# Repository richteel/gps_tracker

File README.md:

# gps_tracker
GPS Tracker and data logger

The files here include hardware, case, PCB, Python and C++ code, documentation, and reference files.

## Bill of Materials (BOM) ##
- Adafruit Feather RP2040
	- Qty: 1
	- Source: Adafruit [https://www.adafruit.com/product/4884](https://www.adafruit.com/product/4884 "Adafruit Feather RP2040")
- Adafruit Micro SD Breakout
	- Qty: 1
	- Source: Adafruit [https://www.adafruit.com/product/4682](https://www.adafruit.com/product/4682 "Adafruit Micro SD SPI or SDIO Card Breakout Board - 3V ONLY!")
- SPDT Slide Switch
	- Qty: 2
	- Source: Adafruit [https://www.adafruit.com/product/805](https://www.adafruit.com/product/805 "SPDT Slide Switch")
- Tactile Switch Push Button (6mm slim)
	- Qty: 4
	- Source: Adafruit [https://www.adafruit.com/product/1489](https://www.adafruit.com/product/1489 "Tactile Switch Push Button (6mm slim)")
- ST-PH 2-Pin SMT Right Angle Connector
	- Qty: 1
	- Source: Adafruit [https://www.adafruit.com/product/1769](https://www.adafruit.com/product/1769 "ST-PH 2-Pin SMT Right Angle Connector")
- GPS Receiver - GP-635T (50 Channel)
	- Qty: 1
	- Source: Sparkfun [https://www.sparkfun.com/products/retired/11571](https://www.sparkfun.com/products/retired/11571 "GPS Receiver - GP-635T (50 Channel)")
- JST SH Jumper 6 Wire Assembly - 8"
	- Qty: 1
	- Source: Sparkfun [https://www.sparkfun.com/products/10361](https://www.sparkfun.com/products/10361 "JST SH Jumper 6 Wire Assembly - 8 inch")
- I2C 128x64 OLED Display
	- Qty: 1
	- Source: Amazon [https://www.amazon.com/gp/product/B08VNRH5HR/ref=ppx_yo_dt_b_search_asin_title?ie=UTF8&th=1](https://www.amazon.com/gp/product/B08VNRH5HR/ref=ppx_yo_dt_b_search_asin_title?ie=UTF8&th=1 "I2C 128x64 OLED Display")
- 3.7V 680mAh 102530 Lipo Battery Rechargeable Lithium Polymer ion Battery Pack with JST Connector
	- Qty: 1
	- Source: Amazon [https://www.amazon.com/gp/product/B07BTPNS2B/ref=ppx_yo_dt_b_search_asin_title?ie=UTF8&psc=1](https://www.amazon.com/gp/product/B07BTPNS2B/ref=ppx_yo_dt_b_search_asin_title?ie=UTF8&psc=1 "3.7V 680mAh 102530 Lipo Battery Rechargeable Lithium Polymer ion Battery Pack with JST Connector")
	- **WARNING:** The battery from this source has reversed polarity. Change the pins to match correct orientation!
- CR2032 Coin Button Cell Battery Holder Case
	- Qty: 1
	- Source: Amazon [https://www.amazon.com/gp/product/B06XF3K4NP/ref=ppx_yo_dt_b_search_asin_image?ie=UTF8&psc=1](https://www.amazon.com/gp/product/B06XF3K4NP/ref=ppx_yo_dt_b_search_asin_image?ie=UTF8&psc=1 "CR2032 Coin Button Cell Battery Holder Case")
- CR2032 Battery
	- Qty: 1
	- Source: Battery Junction [https://www.batteryjunction.com/sony-cr2032-5pack](https://www.batteryjunction.com/sony-cr2032-5pack "CR2032 Battery")
- Resistor 4.7K Ω (0805 package)
	- Qty: 4
	- Source: DigiKey [https://www.digikey.com/en/products/filter/chip-resistor-surface-mount/52...](https://www.digikey.com/en/products/filter/chip-resistor-surface-mount/52?s=N4IgjCBcoEwAwA4CsVQGMoDMCGAbAzgKYA0IA9lANogAsAdAOwAEA1gPIAWAtviALqkADgBcoIAKoA7AJbC2mALKFs%2BAK4AnQiAC%2BpALQxUIDJGHrVJclRAo%2BukHoCcRk2YukKkahDv3DXkEQ4JCZNfGl8YTJ1flIUaBBBKDAhJMgYJHsANiNpABMxPTA4CCFRSBAQUmEAT0EtCpUMbW0gA ""Filter for Resistor 4.7K Ω (0805 package)")
- Resistor 2M Ω (0805 package)
	- Qty: 4
	- Source: DigiKey [https://www.digikey.com/en/products/filter/chip-resistor-surface-mount/52...](https://www.digikey.com/en/products/filter/chip-resistor-surface-mount/52?s=N4IgjCBcoEwAwA4CsVQGMoDMCGAbAzgKYA0IA9lANogwAEAsgPIAWAtviALqkAOALlBABVAHYBLPo0z1C2fAFcAToRABfUgFoYqEBkh9F8kuSogUndSA0BOHXoNHSFSNQgXL2lyERwktZfhi%2BHxkilykKNAgPFBgvDGQMEiWAGw6YgAmghpgcBC8ApAgIKR8AJ48KkVyGKqqQA ""Filter for Resistor 2M Ω (0805 package)") 
- Capacitor 0.1μF (0805 package)
	- Qty: 2
	- Source: DigiKey [https://www.digikey.com/en/products/filter/ceramic-capacitors/60...](https://www.digikey.com/en/products/filter/ceramic-capacitors/60?s=N4IgjCBcoEwAwBYCcVQGMoDMCGAbAzgKYA0IA9lANohwB0YABAK0BiIAuqQA4AuUIAVQB2ASx4B5TAFlC2fAFcAToRABfUgFoYqEBkg9F8kuSogArB3UgNKaLqgGjpCpGoR2qq9tc0AHHDMGAGFsLmw0MTJFDlIANh0RABN%2BDTA4CG4%2BSBAQUh4ATy4VbLkMTyA "Filter for Capacitor 0.1μF (0805 package)")
- PCB
	- Qty: 1
	- Source: Shared on OSH Park [https://oshpark.com/shared_projects/GzuBZVdm](https://oshpark.com/shared_projects/GzuBZVdm "PCB")

# Log File #

The GPS Log Files are named with the format of YYYYMMDD.txt, where the letters are the following:

- YYYY: 4-digit Year
- MM: 2-digit Month
- DD: 2-digit Day

The data is comma separated, with the following columns.

- ISO 8601 formatted time-stamp (UTC) e.g. 2009-10-17T18:37:26Z
- Latitude in Degrees
- Longitude in Degrees
- Elevation in Meters
- Heading in Degrees
- Speed in Kpm

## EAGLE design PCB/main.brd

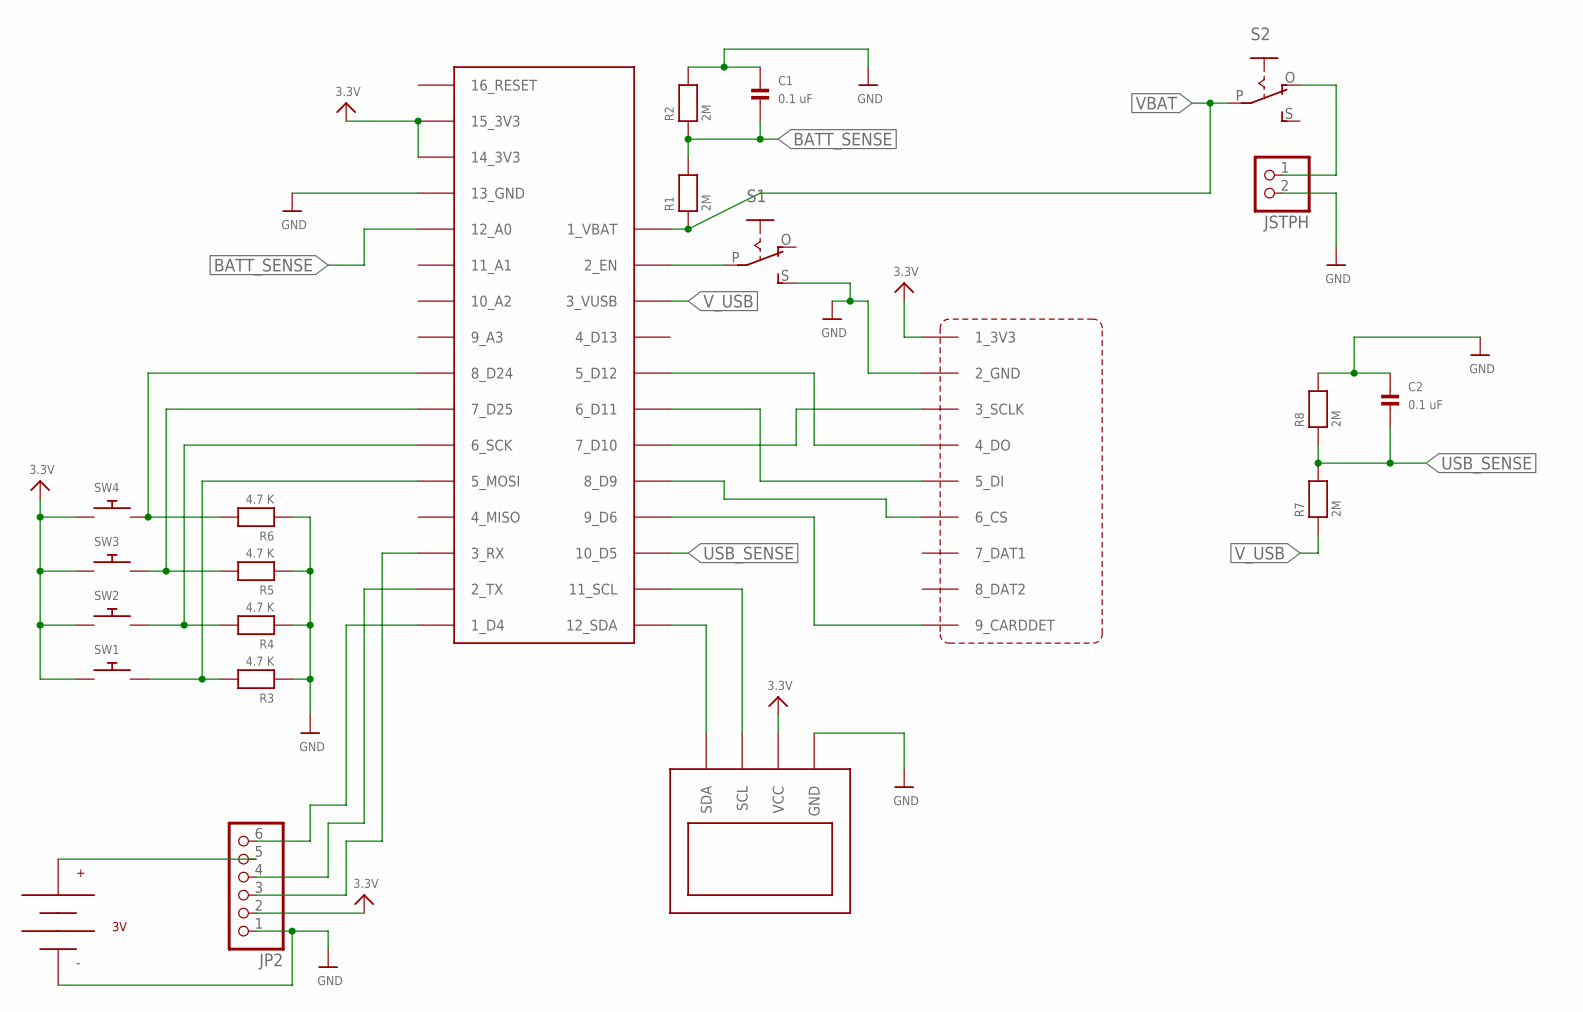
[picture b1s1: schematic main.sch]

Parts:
BAT_1: CR2032_HOLDER_WMYCONGCONG
C1, C2: 0.1 uF; _0805
FEATHER_RP2040: ADAFRUIT_FEATHER_RP2040; ADAFRUIT_FEATHER
JP2: HEADER-1X6ROUND; 1X06_ROUND
JSTPH: JST_2PIN-SMT-RA; JST-PH-2-SMT-RA
R1, R2, R7, R8: 2M; 0805
R3, R4, R5, R6: 4.7 K; 0805
S1, S2: EG1218S; EG1218
SDCARD2: ADAFRUIT_SDCARD3V3BOTTOM_MNT; ADAFRUIT_SDCARD3V3_B
SW1, SW2, SW3, SW4: SWITCH_PUSHBUTTONEVQ-PE; TACT_PANA-EVQ
U$10: OLED_SDD1306_128X64FRIENDA; OLED_SDD1306_128X64

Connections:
3.3V: FEATHER_RP2040.14_3V3, FEATHER_RP2040.15_3V3, JP2.2, SDCARD2.1_3V3, SW1.P$1, SW2.P$1, SW3.P$1, SW4.P$1, U$10.2_VCC (VCC)
BATT_SENSE: C1.2, FEATHER_RP2040.12_A0, R1.2, R2.1
GND: BAT_1.V- (-), C1.1, C2.1, FEATHER_RP2040.13_GND, JP2.1, JSTPH.2 (1), R2.2, R3.1, R4.1, R5.1, R6.1, R8.2, S1.S, SDCARD2.2_GND, U$10.1_GND (GND)
unnamed: FEATHER_RP2040.9_D6, SDCARD2.9_CARDDET
unnamed: FEATHER_RP2040.5_D12, SDCARD2.4_DO
unnamed: FEATHER_RP2040.7_D10, SDCARD2.3_SCLK
unnamed: FEATHER_RP2040.6_D11, SDCARD2.5_DI
unnamed: FEATHER_RP2040.8_D9, SDCARD2.6_CS
unnamed: FEATHER_RP2040.2_EN, S1.P
unnamed: FEATHER_RP2040.8_D24, R6.2, SW4.P$2
unnamed: FEATHER_RP2040.7_D25, R5.2, SW3.P$2
unnamed: FEATHER_RP2040.6_SCK, R4.2, SW2.P$2
unnamed: FEATHER_RP2040.5_MOSI, R3.2, SW1.P$2
unnamed: BAT_1.V+ (+), JP2.5
unnamed: FEATHER_RP2040.12_SDA, U$10.4_SDA (SDA)
unnamed: FEATHER_RP2040.11_SCL, U$10.3_SCL (SCL)
unnamed: JSTPH.1 (2), S2.O
unnamed: FEATHER_RP2040.3_RX, JP2.3
unnamed: FEATHER_RP2040.2_TX, JP2.4
unnamed: FEATHER_RP2040.1_D4, JP2.6
USB_SENSE: C2.2, FEATHER_RP2040.10_D5, R7.2, R8.1
VBAT: FEATHER_RP2040.1_VBAT, R1.1, S2.P
V_USB: FEATHER_RP2040.3_VBUS (3_VUSB), R7.1

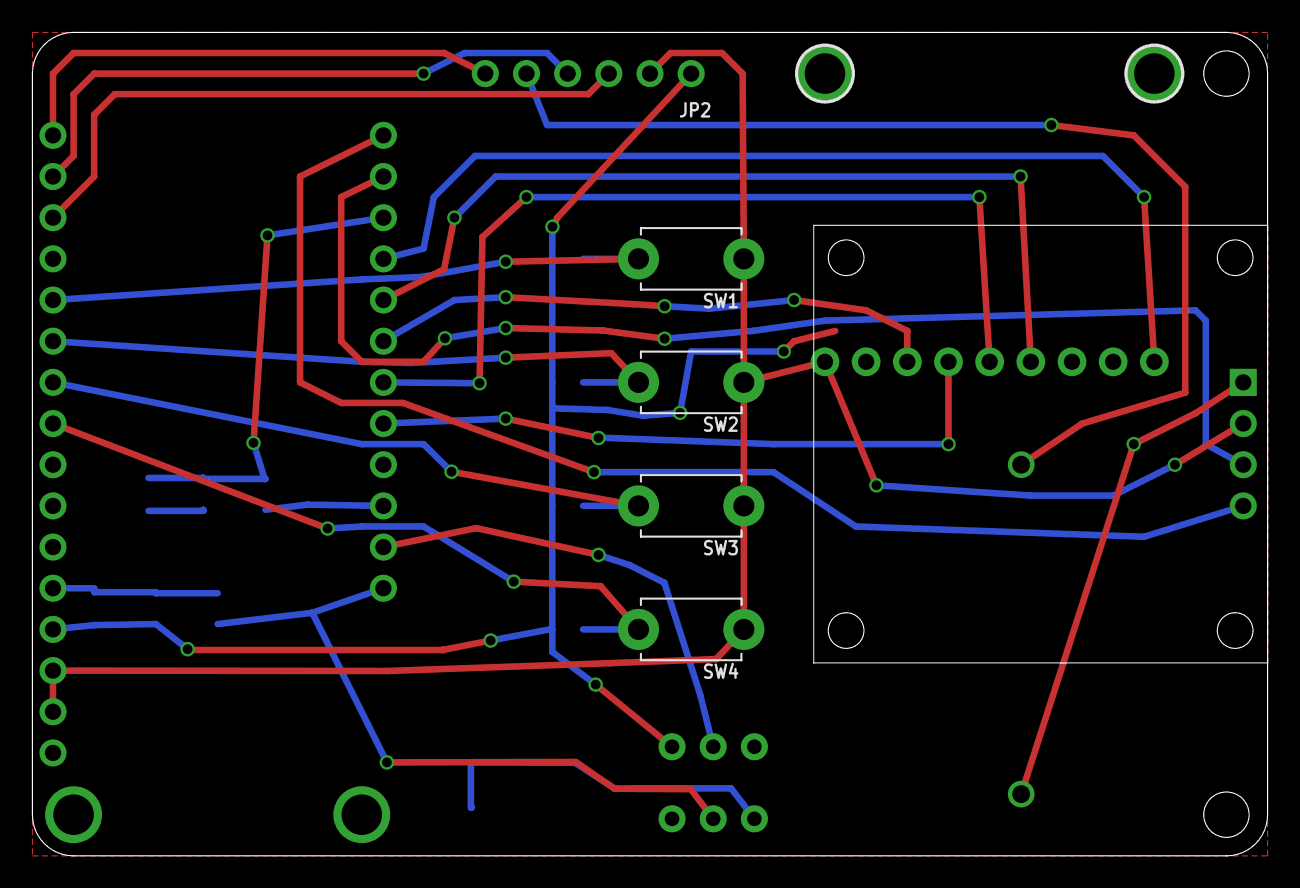
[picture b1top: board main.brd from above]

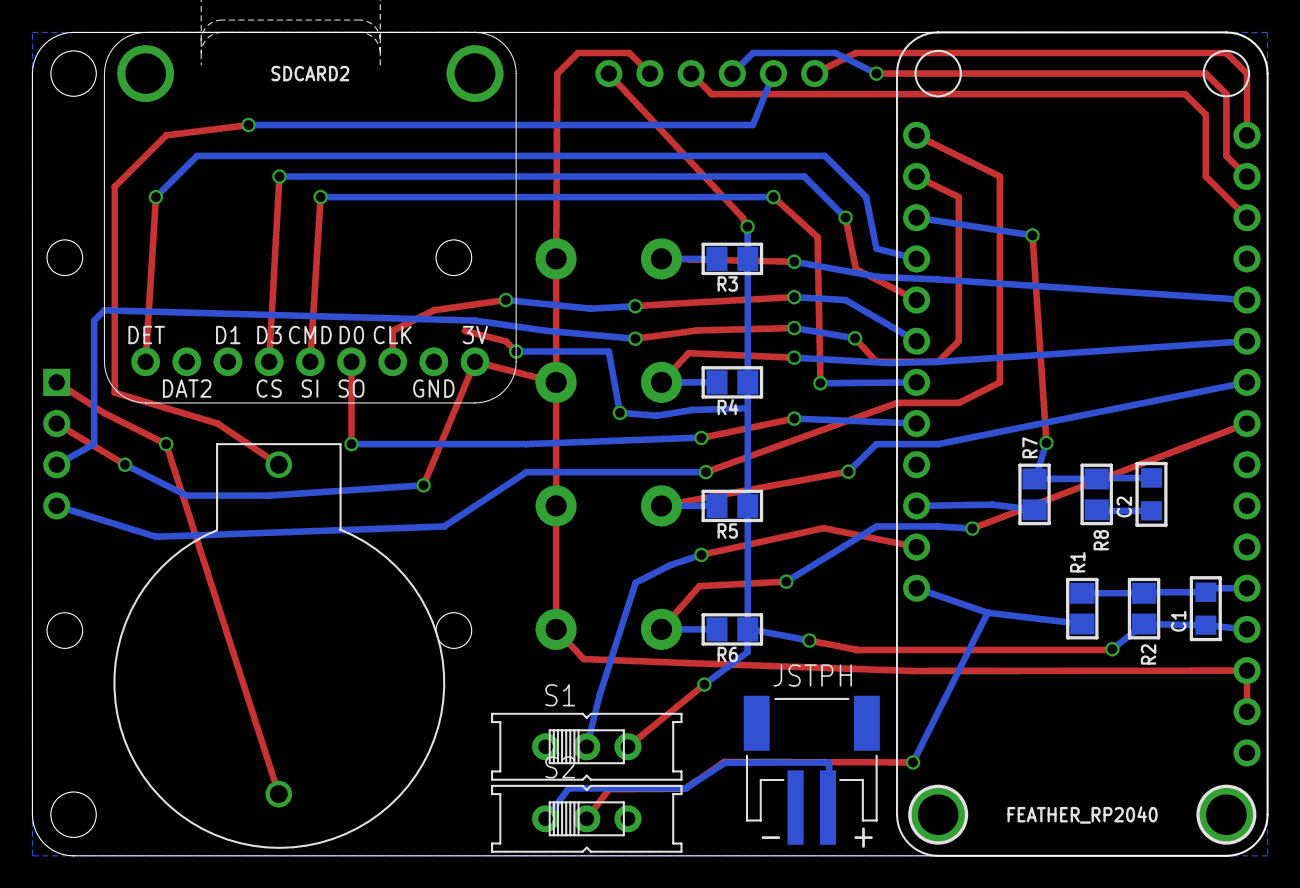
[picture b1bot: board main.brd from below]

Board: 2 copper layers, 76.2 x 50.8 mm, 22 parts (15 on the bottom side), 23 nets.

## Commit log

2021-09-18 Initial
2021-10-09 Updated CircuitPython code and added PCB Design (sent to OSH Park)
2021-10-22 Appears to be the most stable code thus far with very responsive button and SD Card handling. May have issues with the log files with the date missing sometimes.
2021-10-24 Fixed an issue with log file format No tab delimiters due to forgetting to increment the column count
2021-10-24 Files for the case
2021-10-27 Fixed small issue with battery icon and adjusted min and max voltages
2021-11-13 Updates to front and back covers
2021-11-13 Updated Case
2021-11-13 Updated PCB
2021-11-15 Added UBLOX Documentation
2023-12-29 Updating Arduino C++ Version and documentation
2023-12-29 Moved Tests to separate folder
2024-01-06 Fixed an issue with the GPS Log file name. Day was not formatted properly, so there was a space for one digit days. The format should have been day padded with a zero.
    202401 6.txt should have been 20240106.txt
2024-01-07 Formatted the output of the CSV File to match GPSBabel Universal CSV format.
2024-01-25 - Removed Neopixel light option - Added auto display off functionality

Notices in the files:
parts and their libraries:
microbuilder: This work is placed in the public domain, and may be freely used for commercial and non-commercial work with the following conditions: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
